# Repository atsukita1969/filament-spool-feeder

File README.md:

# Filament Spool Feeder for Direct-Drive 3D Printers
# ダイレクト式3Dプリンタ用 フィラメントスプールフィーダー

[日本語](#日本語) | [English](#english)

---

## 日本語

### 概要

ダイレクト式（エクストルーダーがヘッドに載っている方式）の3Dプリンタでは、フィラメントをスプールから引き出す力がすべてエクストルーダーにかかります。次のような場面で、フィラメントの引き込みに抵抗がかかり、吐出量が減って品質が落ちます。

- スプールが重い（特に1kg）
- 高速で印刷する
- ノズルがテーブル上でXY方向に大きく移動し、その移動量の分だけフィラメントが引っ張られる

広い部屋ならスプールをプリンタから離して、遊びのフィラメントを長く取れば防げますが、ホビー用途ではその場所がありません。このフィーダーは、ボーデン式とダイレクト式を組み合わせる考え方で、スプールを能動的に回してフィラメントを先に送り出しておく装置です。

### しくみ

1. スプールをウレタンローラーに載せ、ステッピングモーターでGT2ベルトを介してローラーを回します。
2. フィラメントはゴム紐につながったレバーを通ります。一定以上引っ張られるとスイッチが入り、モーターが回ってスプールから送り出します。
3. スイッチが切れた後も一定量（4000ステップ）送り出してから止まります。フィラメントは使用量より多めに送り出され、ゴム紐の伸びとフィラメントのたるみで200mm以上の余裕ができます。
4. 送り要求が異常に長く続いた場合（ジャム）は、独立したマイコン（ATtiny85）がリレーでモーター電源を切り、停止状態を保持します。

詳しくは [docs/principle.md](docs/principle.md) を参照してください。

### リポジトリの構成

| フォルダ | 内容 |
|:--|:--|
| [firmware/](firmware/) | Arduino Pro Mini（メイン制御）と ATtiny85（ジャム監視）のファームウェア |
| [hardware/pcb/](hardware/pcb/) | 制御基板 rev.B（EAGLE データ、回路図 PDF、BOM） |
| [hardware/mechanical/](hardware/mechanical/) | 機構部品（組立外形図、自作部品の STEP データ、BOM） |
| [docs/](docs/) | 原理、配線、画像 |
| [tools/sim/](tools/sim/) | ファームの検証に使った AVR シミュレーション環境 |

### はじめに

1. 機構: [hardware/mechanical/](hardware/mechanical/) の組立外形図、BOM、自作部品の STEP データで組み立てます。
2. 基板: [hardware/pcb/](hardware/pcb/) の EAGLE データで製作します。配線は [docs/wiring.md](docs/wiring.md) にあります。
3. ファーム: [firmware/](firmware/) の手順で、Pro Mini と ATtiny85 に書き込みます。rev.B 基板では、ATtiny85 のファームの `EXT_SENSE_ENABLED` を 1 にします。

### 状態表示LED（改版基板 rev.B）

| LED | 意味 |
|:--|:--|
| 点灯 | 送り要求中 |
| ゆっくり点滅（約1秒周期） | モータードライバが使えない（ジャム監視がモーター電源を切った、など） |
| 速い点滅（約0.25秒周期） | 異常で停止・保持中（リセットで復帰） |
| 消灯 | 待機中 |

### ライセンス

| 対象 | ライセンス |
|:--|:--|
| ハードウェア設計（hardware/） | [CERN-OHL-S-2.0](LICENSES/CERN-OHL-S-2.0.txt) |
| ファームウェアとツール（firmware/, tools/） | [GPL-3.0-or-later](LICENSES/GPL-3.0.txt) |
| 文書と画像（docs/, README など） | [CC BY-SA 4.0](LICENSES/CC-BY-SA-4.0.txt) |

他者のライブラリ、EAGLE ライブラリ要素、購入部品の 3D モデルは対象外です。詳細は [LICENSE.md](LICENSE.md) を参照してください。変更履歴は [CHANGELOG.md](CHANGELOG.md) にあります。2023年に公開した元の状態は、タグ `v1.0-2023` で参照できます。

---

## English

### Overview

On a direct-drive 3D printer (extruder mounted on the print head), the extruder alone has to pull the filament off the spool. The pull resistance reduces the extruded amount and degrades print quality when:

- the spool is heavy (especially 1 kg spools),
- printing fast,
- the nozzle makes long XY travel moves, which pull the filament by the travel distance.

In a large room you can place the spool far from the printer to get a long slack loop, but hobby spaces rarely allow that. This feeder combines the ideas of Bowden and direct drive: it actively turns the spool and pays out filament in advance.

### How it works

1. The spool rests on a urethane roller, driven by a stepper motor through a GT2 belt.
2. The filament passes a lever held by an elastic cord. When the filament is pulled beyond a threshold, a switch closes and the motor turns the spool to pay out filament.
3. After the switch opens, the motor keeps feeding a fixed amount (4000 steps) and stops. More filament is paid out than consumed; the elastic cord and the slack provide more than 200 mm of buffer.
4. If the feed request lasts abnormally long (jam), an independent microcontroller (ATtiny85) cuts the motor supply with a relay and latches the stop.

See [docs/principle.md](docs/principle.md) for details.

### Repository layout

| Folder | Contents |
|:--|:--|
| [firmware/](firmware/) | Firmware for the Arduino Pro Mini (main control) and the ATtiny85 (jam monitor) |
| [hardware/pcb/](hardware/pcb/) | Control board rev.B (EAGLE files, schematic PDF, BOM) |
| [hardware/mechanical/](hardware/mechanical/) | Mechanical parts (outline drawing, STEP files of the self-made parts, BOM) |
| [docs/](docs/) | Principle, wiring, images |
| [tools/sim/](tools/sim/) | AVR simulation used to verify the firmware |

### Getting started

1. Mechanics: build from the outline drawing, the BOM and the STEP files of the self-made parts in [hardware/mechanical/](hardware/mechanical/).
2. Board: make it from the EAGLE files in [hardware/pcb/](hardware/pcb/). Wiring is in [docs/wiring.md](docs/wiring.md).
3. Firmware: flash the Pro Mini and the ATtiny85 as described in [firmware/](firmware/). For board rev.B, set `EXT_SENSE_ENABLED` to 1 in the ATtiny85 firmware.

### Status LED (board rev.B)

| LED | Meaning |
|:--|:--|
| On | Feed requested |
| Slow blink (about 1 s period) | Motor driver not available (e.g. motor supply cut by the jam monitor) |
| Fast blink (about 0.25 s period) | Stopped by a fault and latched (reset to recover) |
| Off | Idle |

### License

| Scope | License |
|:--|:--|
| Hardware design (hardware/) | [CERN-OHL-S-2.0](LICENSES/CERN-OHL-S-2.0.txt) |
| Firmware and tools (firmware/, tools/) | [GPL-3.0-or-later](LICENSES/GPL-3.0.txt) |
| Documentation and images (docs/, README, etc.) | [CC BY-SA 4.0](LICENSES/CC-BY-SA-4.0.txt) |

Third-party libraries, EAGLE library elements and 3D models of purchased parts are not covered. See [LICENSE.md](LICENSE.md). The change history is in [CHANGELOG.md](CHANGELOG.md). The original 2023 state is available as tag `v1.0-2023`.

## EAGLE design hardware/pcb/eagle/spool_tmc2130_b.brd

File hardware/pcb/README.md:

# Control board / 制御基板

[日本語](#日本語) | [English](#english)

---

## 日本語

### ファイル

| ファイル | 内容 |
|:--|:--|
| [eagle/spool_tmc2130_b.sch](eagle/spool_tmc2130_b.sch) | 回路図 rev.B（Autodesk Fusion から EAGLE 9.7.0 形式で書き出し、XML） |
| [eagle/spool_tmc2130_b.brd](eagle/spool_tmc2130_b.brd) | 基板 rev.B（同上、2層、50 × 90 mm） |
| [spool_tmc2130_b_schematic.pdf](spool_tmc2130_b_schematic.pdf) | 回路図 rev.B の PDF（A3） |
| [bom.csv](bom.csv) | 部品表（rev.A の実装品と rev.B） |

EAGLE データは Autodesk Fusion の Electronics で開けます。KiCad でも取り込めます。配線とピン割り当ては [docs/wiring.md](../../docs/wiring.md) にあります。上の画像は rev.A の基板です。

rev.A（製作済み。発注に使ったデータ）は、タグ [`pcb-rev.A`](https://github.com/atsukita1969/filament-spool-feeder/tree/pcb-rev.A/hardware/pcb) から取り出せます。

### rev.A と rev.B に共通の注意点

- GND は配線ではなく表裏のベタだけで接続しています。
- リレー K1 のコイルは 5V 駆動です。部品は G6K-2P-Y **DC5** を使ってください（DC12 品は 5V では動作しません）。

### rev.B の変更点

| # | 変更 | 理由 |
|:--|:--|:--|
| 1 | X5 の2番と JP2 の1番を EXT_IN から外し、新しいネット EXT_SENSE として ATtiny85 PB4（3番ピン）へ接続。R5（10kΩ）でプルダウン | 外部センサーの異常でモーター電源を切れるようにするため（rev.A では ATtiny85 の出力と衝突して機能しない）。HIGH = 正常、LOW または断線 = 異常。JP2 の1-2 短絡で「外部センサーなし」 |
| 2 | EXT_SENSE と PB4 の間に R6（10kΩ）を直列に追加 | X5 に 5V を超える電圧（最大 12V）が加わっても、ATtiny85 の入力保護ダイオードに流れる電流を約 0.65mA に抑えるため |
| 3 | T1 を DTC144EKA から DTC123JKA に変更（同じ SMT3、同じ端子配置） | 入力電流が 68〜126µA から 1.45〜2.69mA に増え、コイル電流 21.1mA で確実に飽和する |
| 4 | R2 を 680Ω から 2.2kΩ に変更 | 抵抗の損失を約 0.045W に下げる |
| 5 | D3 を D4 ネットから外し、Pro Mini D8 → D3 → R4 → GND で駆動。R4 を 150Ω から 470Ω に変更 | X9 にどの種類のセンサーでも接続できるようにし、LED で状態を表示するため。D8 の電流は約 6mA |
| 6 | チップ抵抗 R1〜R6 を 0603 から 0805（2012）に変更 | 手はんだをしやすくするため |

部品の配置：R5 は X5 の近く、R6 は U2 の近くにあります。R2 と R3 は表面、ほかのチップ部品（R1、R4、R5、R6、T1、U1）は裏面です。

### rev.B の使い方

- ATtiny85 のファームは `EXT_SENSE_ENABLED` を 1 にして書き込みます（[firmware/](../../firmware/)）。
- 外部センサーを使わないときは、JP2 の1-2 を短絡します。
- X5 には、正常なときに2番を HIGH にするセンサーをつなぎます。例：1-2 間の常閉接点（正常で閉じ、異常や断線で開く）、または 5〜12V を出力するセンサー。NPN オープンコレクタ出力は HIGH を出せないので、そのままでは使えません。

### rev.B の確認

- DRC は、GND の小さい SMD パッド5か所（T1 のE、R1・R3・R4・R5 の1番）で「銅箔幅」を報告します。パッドの短辺（1.0〜1.03mm）が GND ネットクラスの最小幅 1.524mm より細いためで、パッドはベタに直接つながっています。ほかのエラーはありません。
- 製造データ（CAM 出力のガーバー）の銅箔を解析し、26 ネットすべてが設計どおりにつながり、ショートや孤立した銅箔がないことを確かめました。

### rev.A（製作済み）の注意点

- T1（DTC144EKA）はデータシート上の駆動能力に余裕がありません。実機では動いていますが、rev.B で変更しました。
- R2（680Ω、0603）は 12V で約 0.15W 消費し、一般的な 0603 抵抗の定格 0.1W を超えます。
- ATtiny85 を実装したまま JP2 を短絡しないでください。
- 以前公開していた DesignSpark 版のデータは、EAGLE からの変換時に GND ベタが GND ネットから外れていたため削除しました。タグ `v1.0-2023` から参照できます。

ファームは rev.A と rev.B の両方に対応しています（[firmware/](../../firmware/)）。

---

## English

### Files

| File | Contents |
|:--|:--|
| [eagle/spool_tmc2130_b.sch](eagle/spool_tmc2130_b.sch) | Schematic rev.B (exported from Autodesk Fusion in EAGLE 9.7.0 format, XML) |
| [eagle/spool_tmc2130_b.brd](eagle/spool_tmc2130_b.brd) | Board rev.B (same format, 2 layers, 50 × 90 mm) |
| [spool_tmc2130_b_schematic.pdf](spool_tmc2130_b_schematic.pdf) | Schematic rev.B as PDF (A3) |
| [bom.csv](bom.csv) | Bill of materials (rev.A as built and rev.B) |

The EAGLE files open in Autodesk Fusion Electronics and can be imported into KiCad. Wiring and pin assignment are in [docs/wiring.md](../../docs/wiring.md). The picture above shows the rev.A board.

rev.A (built; the data used for fabrication) is available in tag [`pcb-rev.A`](https://github.com/atsukita1969/filament-spool-feeder/tree/pcb-rev.A/hardware/pcb).

### Notes for both rev.A and rev.B

- GND is connected only through the top and bottom copper pours, not by traces.
- The coil of relay K1 is driven from 5 V. Use G6K-2P-Y **DC5** (the DC12 version does not operate on 5 V).

### Changes in rev.B

| # | Change | Reason |
|:--|:--|:--|
| 1 | Disconnect X5 pin 2 and JP2 pin 1 from EXT_IN and route them as a new net EXT_SENSE to ATtiny85 PB4 (pin 3), with a 10 kΩ pull-down R5 | Lets an external sensor cut the motor supply (on rev.A it conflicts with the ATtiny85 output and does not work). HIGH = OK, LOW or broken wire = fault. JP2 1-2 fitted = no external sensor |
| 2 | Add R6 (10 kΩ) in series between EXT_SENSE and PB4 | Limits the current into the input protection diode of the ATtiny85 to about 0.65 mA when more than 5 V (up to 12 V) is applied to X5 |
| 3 | T1: DTC144EKA → DTC123JKA (same SMT3 package and pinout) | Input current rises from 68–126 µA to 1.45–2.69 mA, so the transistor saturates reliably at the 21.1 mA coil current |
| 4 | R2: 680 Ω → 2.2 kΩ | Reduces the resistor dissipation to about 0.045 W |
| 5 | Disconnect D3 from the D4 net and drive it from Pro Mini D8 → D3 → R4 → GND; R4: 150 Ω → 470 Ω | Any type of sensor can then be used on X9, and the LED shows the status. D8 current about 6 mA |
| 6 | Chip resistors R1–R6: 0603 → 0805 (2012) | Easier hand soldering |

Placement: R5 is near X5 and R6 is near U2. R2 and R3 are on the top side; the other chip parts (R1, R4, R5, R6, T1, U1) are on the bottom side.

### Using rev.B

- Flash the ATtiny85 with `EXT_SENSE_ENABLED` set to 1 ([firmware/](../../firmware/)).
- Fit JP2 1-2 when no external sensor is used.
- Connect a sensor to X5 that drives pin 2 HIGH when everything is OK, for example a normally closed contact between pins 1 and 2 (closed = OK, open or broken wire = fault), or a sensor with a 5–12 V output. An NPN open-collector output cannot drive HIGH and does not work as is.

### Checks on rev.B

- The DRC reports "copper width" at five small GND SMD pads (T1 E, pin 1 of R1, R3, R4 and R5). The short side of these pads (1.0–1.03 mm) is narrower than the 1.524 mm minimum width of the GND net class; the pads are connected directly to the pour. There are no other errors.
- The copper of the manufacturing data (Gerber files from the CAM processor) was analysed: all 26 nets are connected as designed, with no shorts and no isolated copper.

### Notes on rev.A (built)

- T1 (DTC144EKA) has no guaranteed drive margin according to its datasheet. It works on the built boards but was changed in rev.B.
- R2 (680 Ω, 0603) dissipates about 0.15 W at 12 V, above the 0.1 W rating of a standard 0603 resistor.
- Do not fit JP2 while the ATtiny85 is installed.
- The DesignSpark files published earlier were removed because the GND pour lost its connection to the GND net in the conversion from EAGLE. They are still available in tag `v1.0-2023`.

The firmware supports both rev.A and rev.B ([firmware/](../../firmware/)).

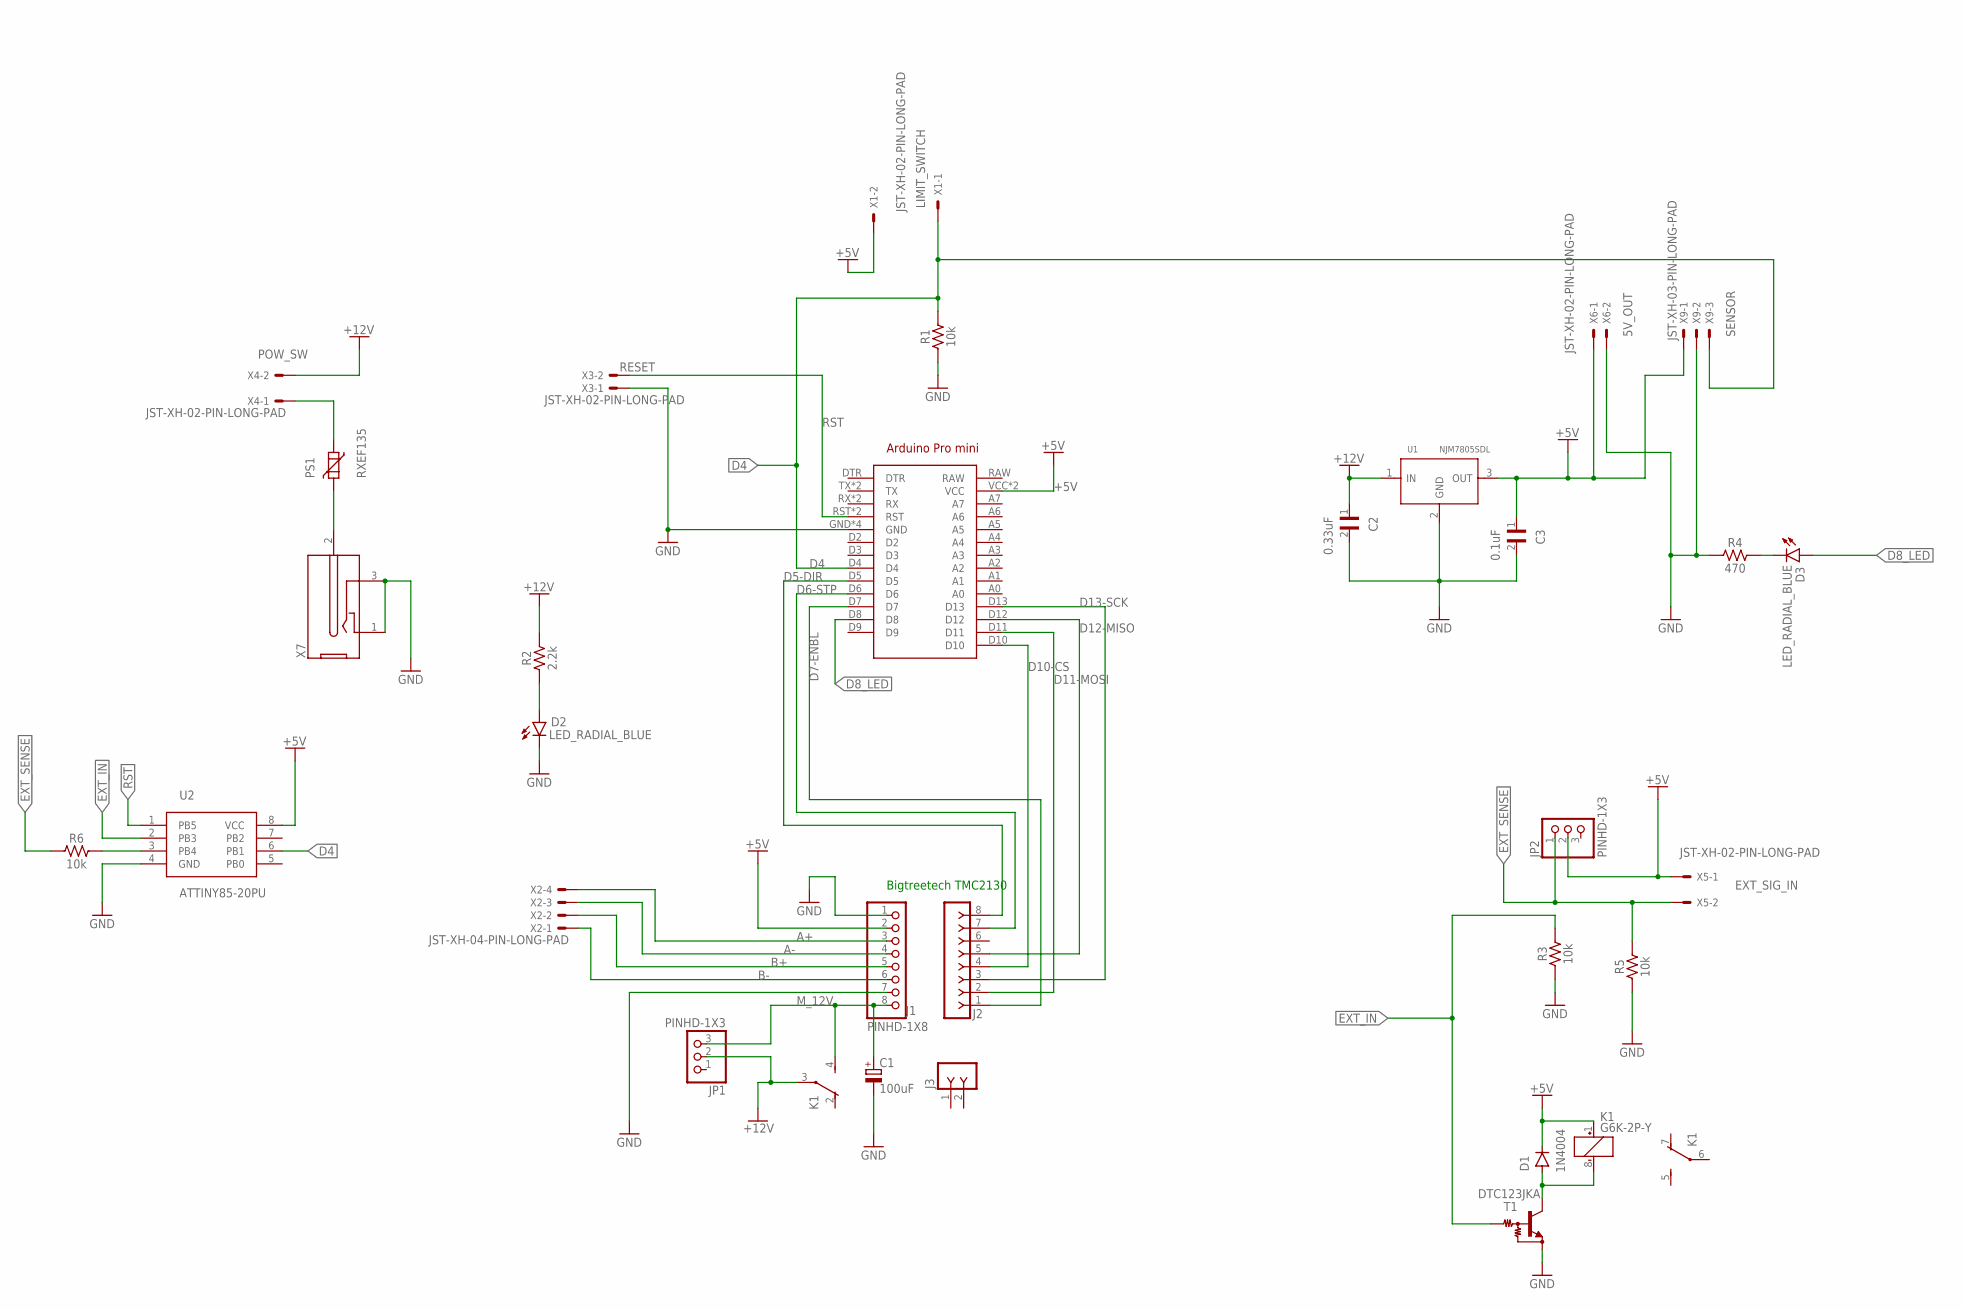
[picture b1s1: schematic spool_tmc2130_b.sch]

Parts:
ARDUINO1: ARDUINO_PRO_MINI
C1: 100uF; E3,5-8
C2: 0.33uF; CAP_RDER73A103K2K1H03B
C3: 0.1uF; CAP_RDER73A103K2K1H03B
D1: 1N4004; DO-41
D2, D3: LED_RADIAL_BLUE; LEDRD254W60D565H860B_B
J1: PINHD-1X8; 1X08
J2: F-1X08-SIP-100-40; SIP-100-08-40
J3: F-1X02-SIP-100-32; SIP-100-02-32
JP1, JP2: PINHD-1X3; 1X03
K1: G6K-2P-Y
PS1: RXEF135; SO5K11
R1, R3, R5, R6: 10k; RESC2012X65
R2: 2.2k; RESC2012X65
R4: 470; RESC2012X65
T1: DTC123JKA; SC59-BEC
U1: NJM7805SDL; TO-252
U2: ATTINY85-20PU; PDIP-8
X1, X3, X4, X5, X6: JST-XH-02-PIN-LONG-PAD; JST-XH-02-PACKAGE-LONG-PAD
X2: JST-XH-04-PIN-LONG-PAD; JST-XH-04-PACKAGE-LONG-PAD
X7: DC-2.1MM-5MM; DC-21MM
X9: JST-XH-03-PIN-LONG-PAD; JST-XH-03-PACKAGE-LONG-PAD

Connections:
+5V: ARDUINO1.VCC, ARDUINO1.VCC@1 (VCC), C3.1, D1.C, J1.2, JP2.2, K1.1 (+), U1.3 (OUT), U2.8 (VCC), X1.2, X5.1, X6.1, X9.1
+12V: C2.1, JP1.2, K1.3, R2.2, U1.1 (IN), X4.2
A+: J1.3, X2.4
A-: J1.4, X2.3
B+: J1.5, X2.2
B-: J1.6, X2.1
D4: ARDUINO1.D4, R1.2, U2.6 (PB1), X1.1, X9.3
D5-DIR: ARDUINO1.D5, J2.8
D6-STP: ARDUINO1.D6, J2.7
D7-ENBL: ARDUINO1.D7, J2.1
D8_LED: ARDUINO1.D8, D3.1 (A)
D10-CS: ARDUINO1.D10, J2.4
D11-MOSI: ARDUINO1.D11, J2.2
D12-MISO: ARDUINO1.D12, J2.5
D13-SCK: ARDUINO1.D13, J2.3
EXT_IN: R3.2, T1.B, U2.2 (PB3)
EXT_SENSE: JP2.1, R5.2, R6.1, X5.2
GND: ARDUINO1.GND, ARDUINO1.GND@1 (GND), ARDUINO1.GND@2 (GND), ARDUINO1.GND@3 (GND), C1.-, C2.2, C3.2, D2.2 (C), J1.1, J1.7, R1.1, R3.1, R4.1, R5.1, T1.E, U1.2 (GND), U2.4 (GND), X3.1, X6.2, X7.1, X7.3 (2), X9.2
M_12V: C1.+, J1.8, JP1.3, K1.4 (S)
unnamed: R6.2, U2.3 (PB4)
unnamed: D3.2 (C), R4.2
unnamed: PS1.1, X4.1
unnamed: PS1.2, X7.2 (3)
unnamed: D2.1 (A), R2.1
unnamed: D1.A, K1.8 (-), T1.C
RST: ARDUINO1.RST, ARDUINO1.RST@1 (RST), U2.1 (PB5), X3.2

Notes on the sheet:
Bigtreetech TMC2130

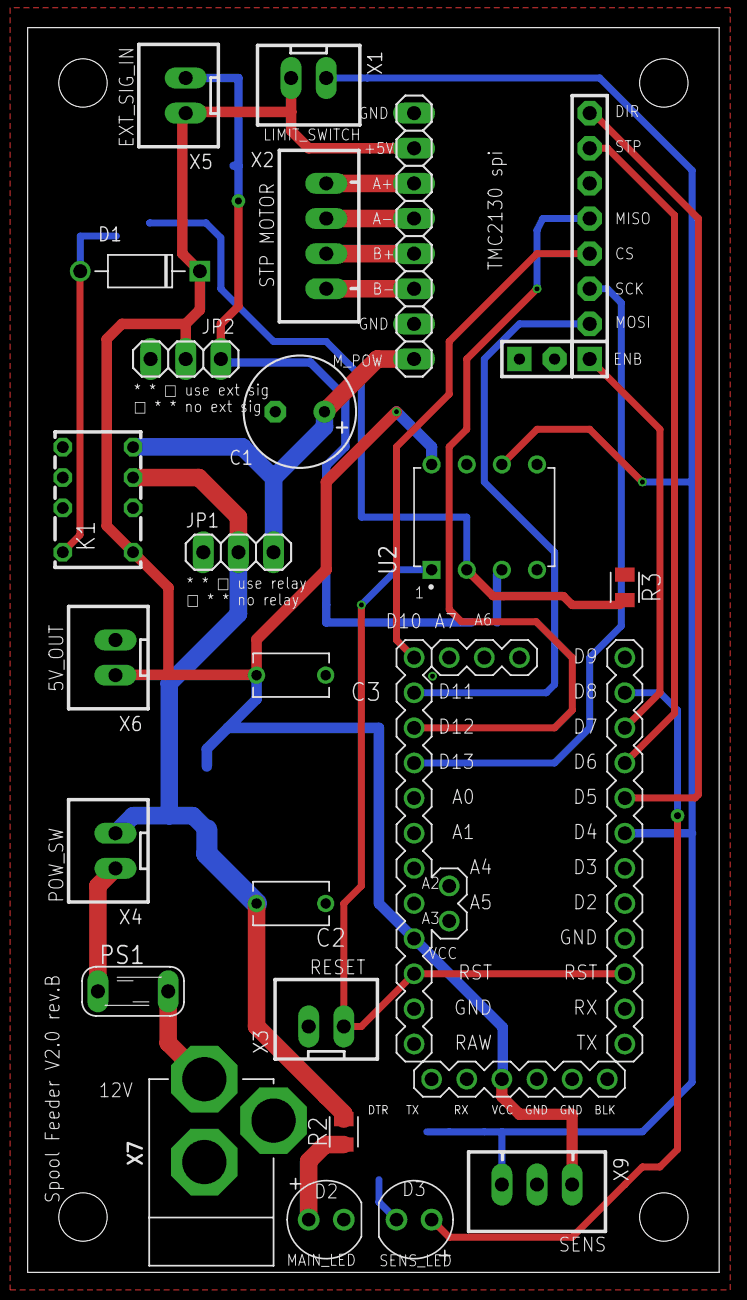
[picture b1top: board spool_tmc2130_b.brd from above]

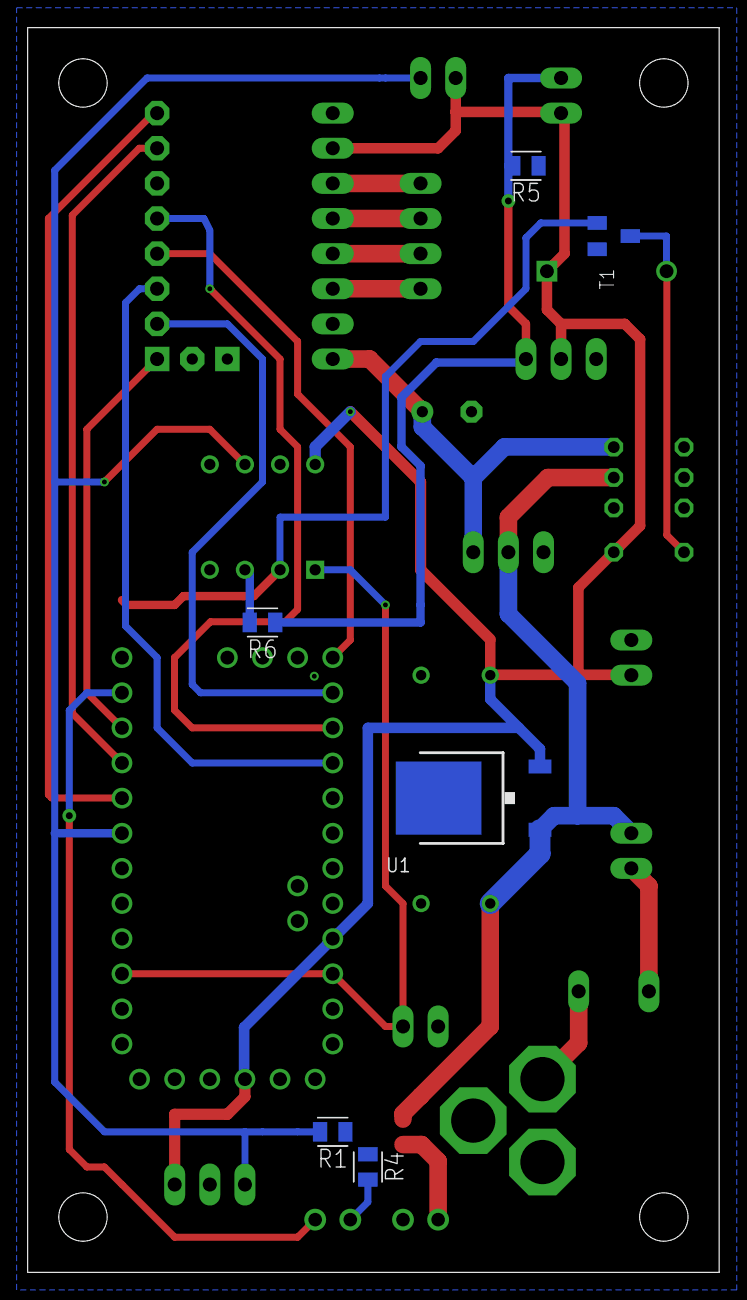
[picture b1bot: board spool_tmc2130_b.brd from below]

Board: 2 copper layers, 50.0 x 90.0 mm, 31 parts (6 on the bottom side), 26 nets.

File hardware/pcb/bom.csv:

ref,qty,rev_a (as built),rev_b (planned),package,function,notes
ARDUINO1,1,Arduino Pro Mini 5V 16MHz (ATmega328P),same,Pro Mini footprint,Main controller,Mounted on pin sockets
U2,1,ATtiny85-20PU,same,DIP-8,Jam monitor,Mounted in a DIP-8 socket
TMC1,1,BIGTREETECH TMC2130 module (SPI),same,StepStick,Stepper driver,Plugged into J1/J2
U1,1,NJM7805SDL,same,TO-252,5V regulator,Bottom side
K1,1,Omron G6K-2P-Y DC5,same,G6K-2P-Y,Motor supply relay,Coil 5 V (DC12 coil does not work on 5 V)
T1,1,ROHM DTC144EKA,ROHM DTC123JKA,SMT3 (SC-59),Relay driver,Bottom side. rev.B: drive margin (R1 2.2k)
D1,1,1N4004,same,DO-41,Relay flyback diode,
D2,1,LED red,same,LED 5mm radial,Power indicator,
D3,1,LED green,same,LED 5mm radial,Feed request / status LED,rev.A: on D4 net. rev.B: driven from Pro Mini D8
C1,1,100uF >=16V aluminum electrolytic,same,Radial 3.5mm pitch dia 8mm,VM bulk capacitor (after relay),
C2,1,0.33uF ceramic,same,Radial 5.0mm pitch,7805 input,
C3,1,0.1uF ceramic,same,Radial 5.0mm pitch,7805 output,
PS1,1,Littelfuse RXEF135,same,Radial 5.08mm pitch,Resettable fuse (hold 1.35 A trip 2.7 A 72 V),
R1,1,10k,same,0603,D4 pull-down,Bottom side
R2,1,680,2.2k,0603,D2 series resistor,rev.A exceeds 0.1 W rating of a standard 0603 at 12 V
R3,1,10k,same,0603,EXT_IN pull-down,Bottom side
R4,1,150,470,0603,D3 series resistor,Bottom side. rev.B: limits D8 current to about 6 mA
R5,1,-,10k,0603,EXT_SENSE pull-down,rev.B only
J1,1,Female header 1x8,same,2.54mm,TMC2130 power side,
J2,1,Female header 1x8,same,2.54mm,TMC2130 logic side,
J3,1,Female header 1x2,same,2.54mm,TMC2130 extra pins,Not connected
JP1,1,Pin header 1x3,same,2.54mm,Relay bypass (2-3),Normally open
JP2,1,Pin header 1x3,same,2.54mm,rev.A: EXT_IN to +5V / rev.B: external sensor not used (1-2),rev.A: do not fit with ATtiny85 installed
X1,1,JST XH 2P,same,XH,Limit switch,
X2,1,JST XH 4P,same,XH,Stepper motor,
X3,1,JST XH 2P,same,XH,Reset switch,Resets Pro Mini and ATtiny85
X4,1,JST XH 2P,same,XH,Power switch,
X5,1,JST XH 2P,same,XH,External input,rev.A: not used / rev.B: to ATtiny85 PB4
X6,1,JST XH 2P,same,XH,5 V output,
X7,1,DC jack 2.1mm,same,DC-21MM,12 V input (center positive),
X9,1,JST XH 3P,same,XH,Sensor input (alternative to X1),

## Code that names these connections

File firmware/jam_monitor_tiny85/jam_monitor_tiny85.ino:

// SPDX-License-Identifier: GPL-3.0-or-later
// Copyright (C) 2023-2026 atsukita1969
// https://github.com/atsukita1969/filament-spool-feeder
/*
 * jam_monitor_tiny85 - independent jam watchdog for the filament spool feeder
 *
 * Target : ATtiny85, ATTinyCore (board "ATtiny25/45/85 (No bootloader)"),
 *          Clock 8 MHz internal, B.O.D. 2.7 V. Run "Burn Bootloader" once to set the fuses.
 *
 * Function
 *   PB1 (pin 6) : feed request, same net as Pro Mini D4 (limit switch X1 / sensor X9).
 *                 HIGH = filament pulled = feed requested. External 10k pull-down (R1).
 *   PB3 (pin 2) : EXT_IN. HIGH -> T1 -> relay K1 closes -> motor supply VM on.
 *                 External 10k pull-down (R3) keeps the relay OFF whenever this pin is not driven.
 *   PB4 (pin 3) : external sensor input (board rev.B only, EXT_SENSE_ENABLED = 1).
 *                 X5 pin 2 with 10k pull-down. HIGH = sensor OK, LOW or open wire = fault.
 *                 Jumper JP (X5 signal to +5V) = external sensor not used.
 *   PB5 (pin 1) : RESET, shared with the Pro Mini reset (X3). X3 also clears a latched fault.
 *
 *   The motor supply is cut and the state is latched until reset / power cycle when
 *     - the feed request stays HIGH continuously for JAM_TIMEOUT_MS (jam), or
 *     - (rev.B) the external sensor reports a fault for EXT_FAULT_FILTER_MS, or is not OK
 *       within EXT_STARTUP_GRACE_MS after power-up.
 *
 * Changes from motor_emergency_stop_tiny85.ino (2023)
 *   - The timer is reset deterministically when the request goes LOW (the old code reset it
 *     only if the input fell during a 10 ms window, so about 1/3 of releases were missed).
 *   - Timeout measured in real time with millis() instead of counting loop passes.
 *     48 s = the effective timeout of the old code at 8 MHz (3000 passes of 10 ms delay
 *     plus Serial output time, measured in simulation: 47.9 s).
 *   - Serial removed: on ATTinyCore its RX shares PB1 and its TX (PB0) is not connected.
 *   - Short LOW glitches (contact chatter) do not reset the timer.
 *   - Fault output is high impedance, so on rev.A boards a fitted jumper on EXT_IN or a signal
 *     on X5 cannot short the pin.
 *   - Watchdog: a hang resets the MCU; a watchdog reset is treated as a fault (fail safe).
 *   - External sensor input for board rev.B.
 */
#include <avr/io.h>
#include <avr/wdt.h>

// ---- Pins (ATTinyCore numbering = PBn) ----
constexpr uint8_t PIN_REQUEST   = 1;   // PB1
constexpr uint8_t PIN_RELAY     = 3;   // PB3
constexpr uint8_t PIN_EXT_SENSE = 4;   // PB4 (rev.B)

// ---- Parameters ----
constexpr uint32_t JAM_TIMEOUT_MS    = 48000UL;  // continuous feed request that is treated as a jam
constexpr uint32_t RELEASE_FILTER_MS = 20UL;     // request must be LOW this long to end an episode

// External sensor (board rev.B). 0 on rev.A boards: PB4 is not connected there.
#ifndef EXT_SENSE_ENABLED                 // can be overridden with -DEXT_SENSE_ENABLED=1
#define EXT_SENSE_ENABLED 0
#endif
constexpr uint32_t EXT_FAULT_FILTER_MS  = 50UL;    // LOW this long while running = sensor fault
constexpr uint32_t EXT_STARTUP_GRACE_MS = 1000UL;  // sensor must report OK within this time

static bool     relayIsOn = false;
static bool     episodeActive = false;
static uint32_t episodeStartMs = 0;
static uint32_t lastHighMs = 0;
#if EXT_SENSE_ENABLED
static bool     extLowTiming = false;
static uint32_t extLowSinceMs = 0;
#endif

static void relayOn() {
  digitalWrite(PIN_RELAY, HIGH);
  pinMode(PIN_RELAY, OUTPUT);
  relayIsOn = true;
}

// Cut the motor supply and stay here until reset / power cycle.
static void latchFault() __attribute__((noreturn));
static void latchFault() {
  digitalWrite(PIN_RELAY, LOW);    // relay off at once
  pinMode(PIN_RELAY, INPUT);       // then high impedance (PORT bit is 0, so no pull-up); R3 holds it LOW
  for (;;) {
    wdt_reset();
  }
}

void setup() {
  const uint8_t resetCause = MCUSR;
  MCUSR = 0;
  wdt_disable();

  pinMode(PIN_REQUEST, INPUT);     // external pull-down R1, no internal pull-up
#if EXT_SENSE_ENABLED
  pinMode(PIN_EXT_SENSE, INPUT);   // external pull-down on rev.B, no internal pull-up
#endif

  wdt_enable(WDTO_1S);
  if (resetCause & _BV(WDRF)) {
    latchFault();                  // previous run hung: do not restart the motor by itself
  }
#if !EXT_SENSE_ENABLED
  relayOn();
#endif
}

void loop() {
  wdt_reset();
  const uint32_t now = millis();

#if EXT_SENSE_ENABLED
  if (digitalRead(PIN_EXT_SENSE) == HIGH) {
    extLowTiming = false;
    if (!relayIsOn) relayOn();     // motor supply only after the sensor has reported OK
  } else {
    if (!extLowTiming) {
      extLowTiming = true;
      extLowSinceMs = now;
    }
    if (relayIsOn && (now - extLowSinceMs) >= EXT_FAULT_FILTER_MS) latchFault();
    if (!relayIsOn && now >= EXT_STARTUP_GRACE_MS) latchFault();
  }
#endif

  if (digitalRead(PIN_REQUEST) == HIGH) {
    lastHighMs = now;
    if (!episodeActive) {
      episodeActive = true;
      episodeStartMs = now;
    } else if (now - episodeStartMs >= JAM_TIMEOUT_MS) {
      latchFault();
    }
  } else if (episodeActive && (now - lastHighMs >= RELEASE_FILTER_MS)) {
    episodeActive = false;         // request released: timer is reset
  }
}

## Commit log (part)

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2023-04-11 Create BOM
2023-04-11 Update BOM
2023-04-11 Rename readme to readme.md

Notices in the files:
parts and their libraries:
con-headers-jp: Copyright (C) 2008, Bob Starr
